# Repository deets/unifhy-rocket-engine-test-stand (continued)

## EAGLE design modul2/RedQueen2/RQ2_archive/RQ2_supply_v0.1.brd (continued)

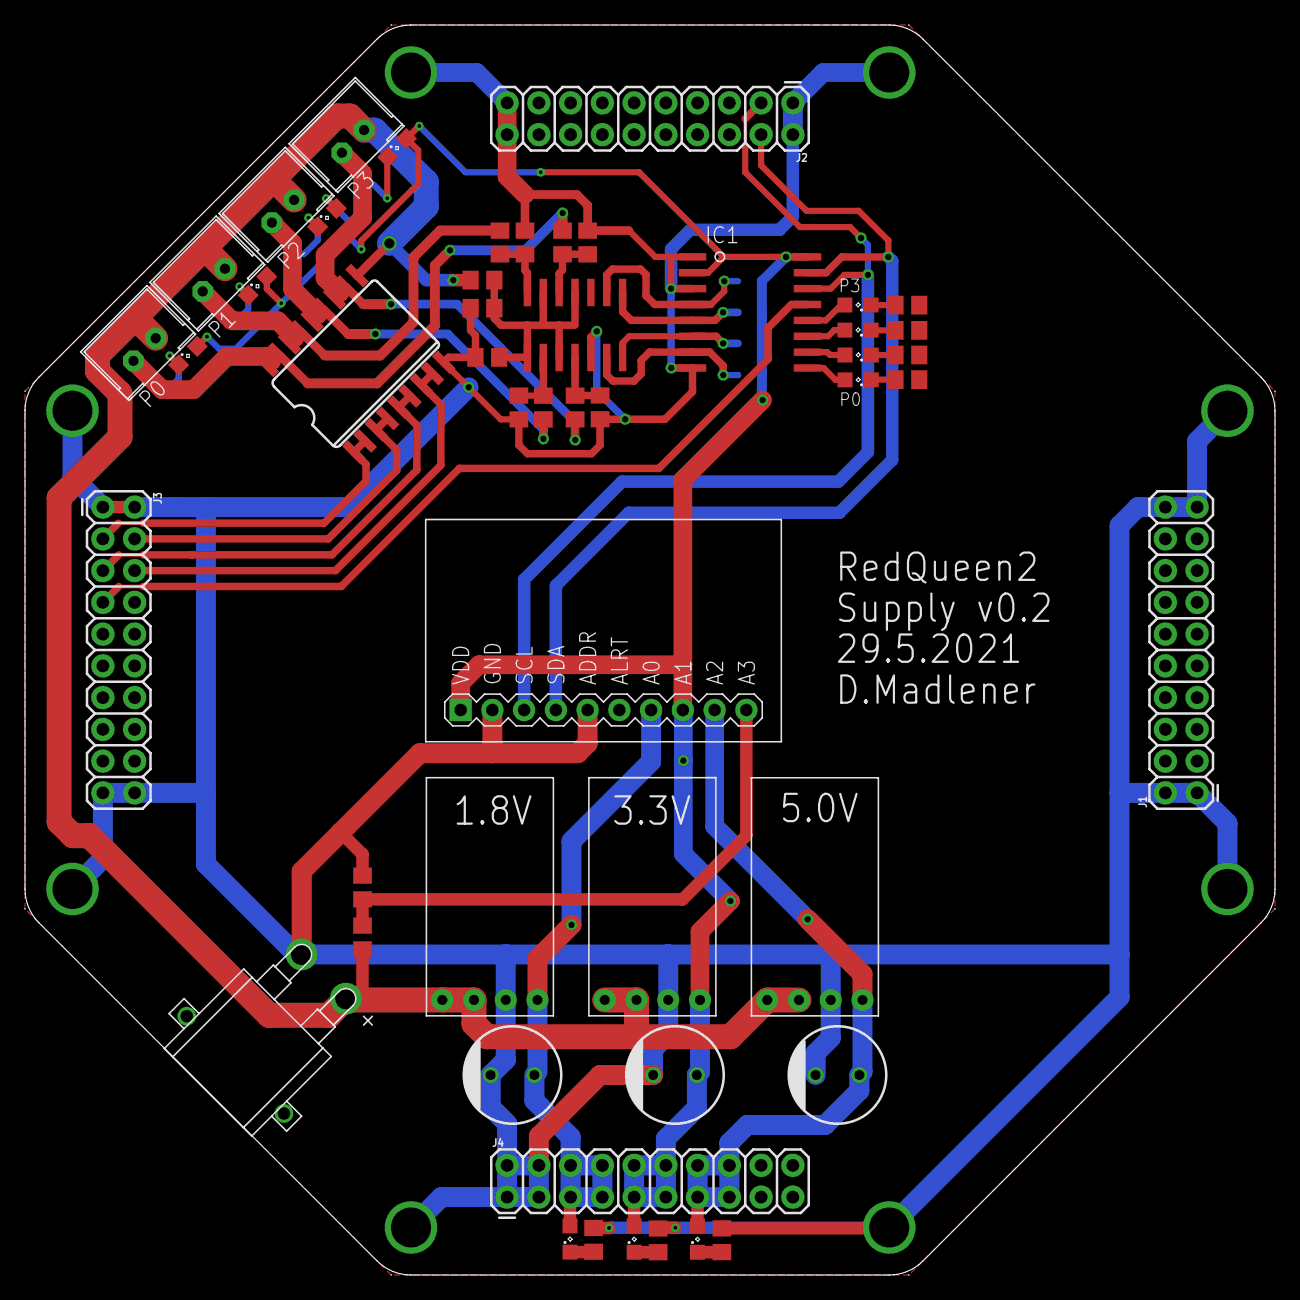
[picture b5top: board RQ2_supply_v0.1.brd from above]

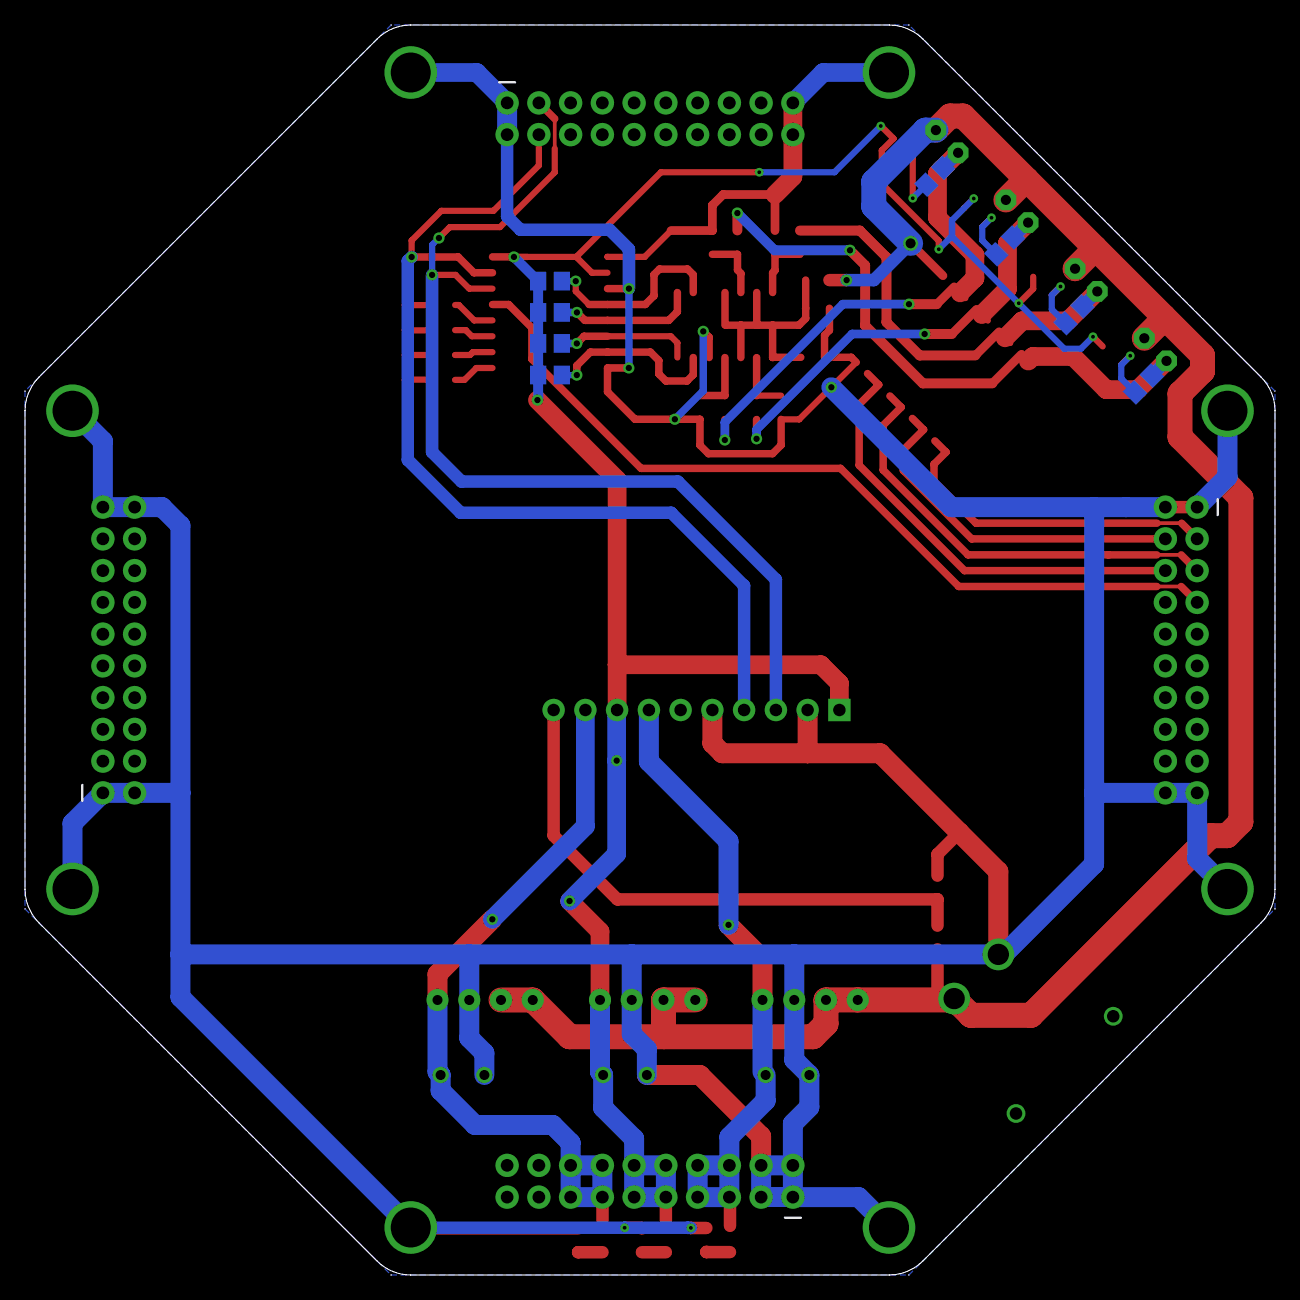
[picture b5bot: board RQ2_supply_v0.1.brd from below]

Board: 2 copper layers, 100.0 x 100.0 mm, 58 parts (8 on the bottom side), 41 nets.

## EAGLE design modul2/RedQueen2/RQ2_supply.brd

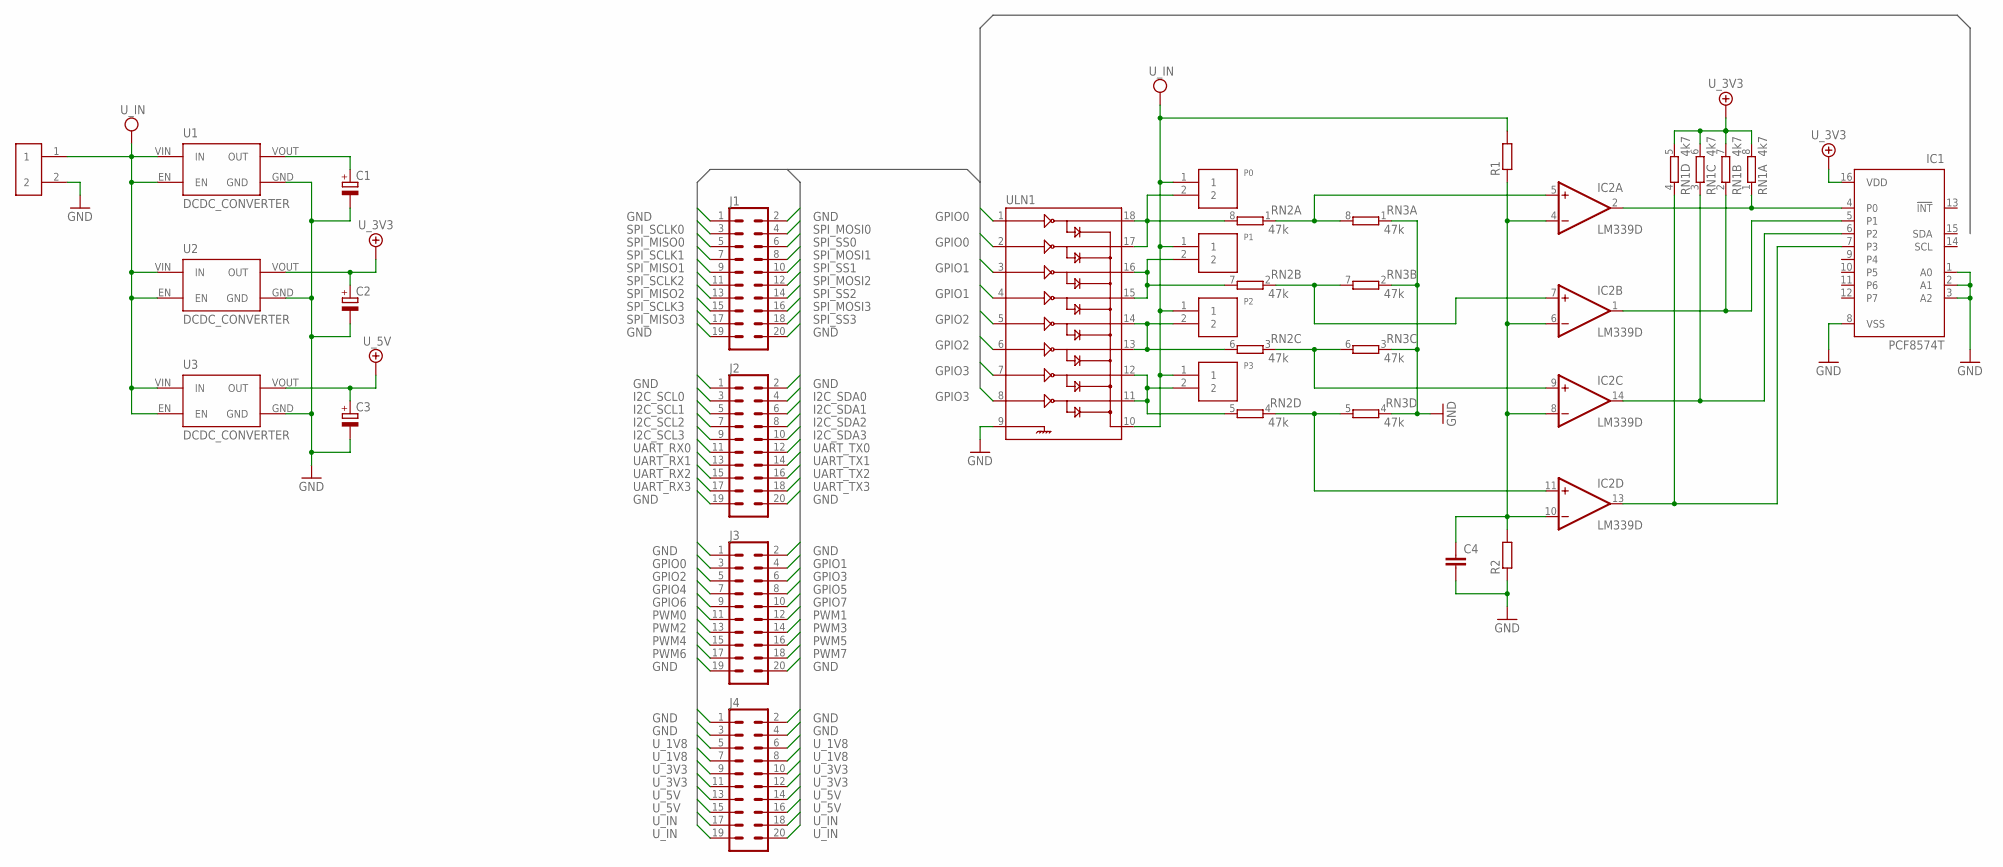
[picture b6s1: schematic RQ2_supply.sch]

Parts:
C1, C2, C3: CPOL-EUC; PANASONIC_C
C4: C-EUC0805; C0805
IC1: PCF8574T; SO16W
IC2: LM339D; SO14
J1, J2, J3, J4: CONN_10X2; 2X10
P0, P1, P2, P3: 2PIN; B2B-PH-K-S
R1, R2: R-EU_R0805; R0805
RN1: 4k7; 0603-ARV
RN2, RN3: 47k; 0603-ARV
U1, U2, U3: DCDC_CONVERTER
U$1: XT_CONN; XT30_PCB
ULN1: ULN2803SOICW; SO18L

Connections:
GND: C1.-, C2.-, C3.-, C4.2, IC1.1 (A0), IC1.2 (A1), IC1.3 (A2), IC1.8 (VSS), IC2.12 (GND), J1.1, J1.2, J1.19, J1.20, J2.1, J2.2, J2.19, J2.20, J3.1, J3.2, J3.19, J3.20, J4.1, J4.2, J4.3, J4.4, R2.1, RN3.1, RN3.2 (1), RN3.3 (1), RN3.4 (1), U1.GND, U2.GND, U3.GND, U$1.2, ULN1.9
GPIO0: J3.3, ULN1.1, ULN1.2
GPIO1: J3.4, ULN1.3, ULN1.4
GPIO2: J3.5, ULN1.5, ULN1.6
GPIO3: J3.6, ULN1.7, ULN1.8
GPIO4: J3.7
GPIO5: J3.8
GPIO6: J3.9
GPIO7: J3.10
I2C_SCL0: J2.3
I2C_SCL1: J2.5
I2C_SCL2: J2.7
I2C_SCL3: J2.9
I2C_SDA0: J2.4
I2C_SDA1: J2.6
I2C_SDA2: J2.8
I2C_SDA3: J2.10
unnamed: IC1.4 (P0), IC2.2 (OUT), RN1.1
unnamed: IC1.5 (P1), IC2.1 (OUT), RN1.2 (1)
unnamed: IC1.6 (P2), IC2.14 (OUT), RN1.3 (1)
unnamed: IC1.7 (P3), IC2.13 (OUT), RN1.4 (1)
unnamed: IC2.5 (+IN), RN2.1, RN3.8 (2)
unnamed: IC2.7 (+IN), RN2.2 (1), RN3.7 (2)
unnamed: IC2.9 (+IN), RN2.3 (1), RN3.6 (2)
unnamed: IC2.11 (+IN), RN2.4 (1), RN3.5 (2)
unnamed: C4.1, IC2.4 (-IN), IC2.6 (-IN), IC2.8 (-IN), IC2.10 (-IN), R1.1, R2.2
PWM0: J3.11
PWM1: J3.12
PWM2: J3.13
PWM3: J3.14
PWM4: J3.15
PWM5: J3.16
PWM6: J3.17
PWM7: J3.18
PYRO0: P0.2, RN2.8 (2), ULN1.17, ULN1.18
PYRO1: P1.2, RN2.7 (2), ULN1.15, ULN1.16
PYRO2: P2.2, RN2.6 (2), ULN1.13, ULN1.14
PYRO3: P3.2, RN2.5 (2), ULN1.11, ULN1.12
SPI_MISO0: J1.5
SPI_MISO1: J1.9
SPI_MISO2: J1.13
SPI_MISO3: J1.17
SPI_MOSI0: J1.4
SPI_MOSI1: J1.8
SPI_MOSI2: J1.12
SPI_MOSI3: J1.16
SPI_SCLK0: J1.3
SPI_SCLK1: J1.7
SPI_SCLK2: J1.11
SPI_SCLK3: J1.15
SPI_SS0: J1.6
SPI_SS1: J1.10
SPI_SS2: J1.14
SPI_SS3: J1.18
UART_RX0: J2.11
UART_RX1: J2.13
UART_RX2: J2.15
UART_RX3: J2.17
UART_TX0: J2.12
UART_TX1: J2.14
UART_TX2: J2.16
UART_TX3: J2.18
U_1V8: C1.+, J4.5, J4.6, J4.7, J4.8, U1.VOUT (OUT)
U_3V3: C2.+, IC1.16 (VDD), J4.9, J4.10, J4.11, J4.12, RN1.5 (2), RN1.6 (2), RN1.7 (2), RN1.8 (2), U2.VOUT (OUT)
U_5V: C3.+, J4.13, J4.14, J4.15, J4.16, U3.VOUT (OUT)
U_IN: J4.17, J4.18, J4.19, J4.20, P0.1, P1.1, P2.1, P3.1, R1.2, U1.EN, U1.VIN (IN), U2.EN, U2.VIN (IN), U3.EN, U3.VIN (IN), U$1.1, ULN1.10
V+: IC2.3 (V+)

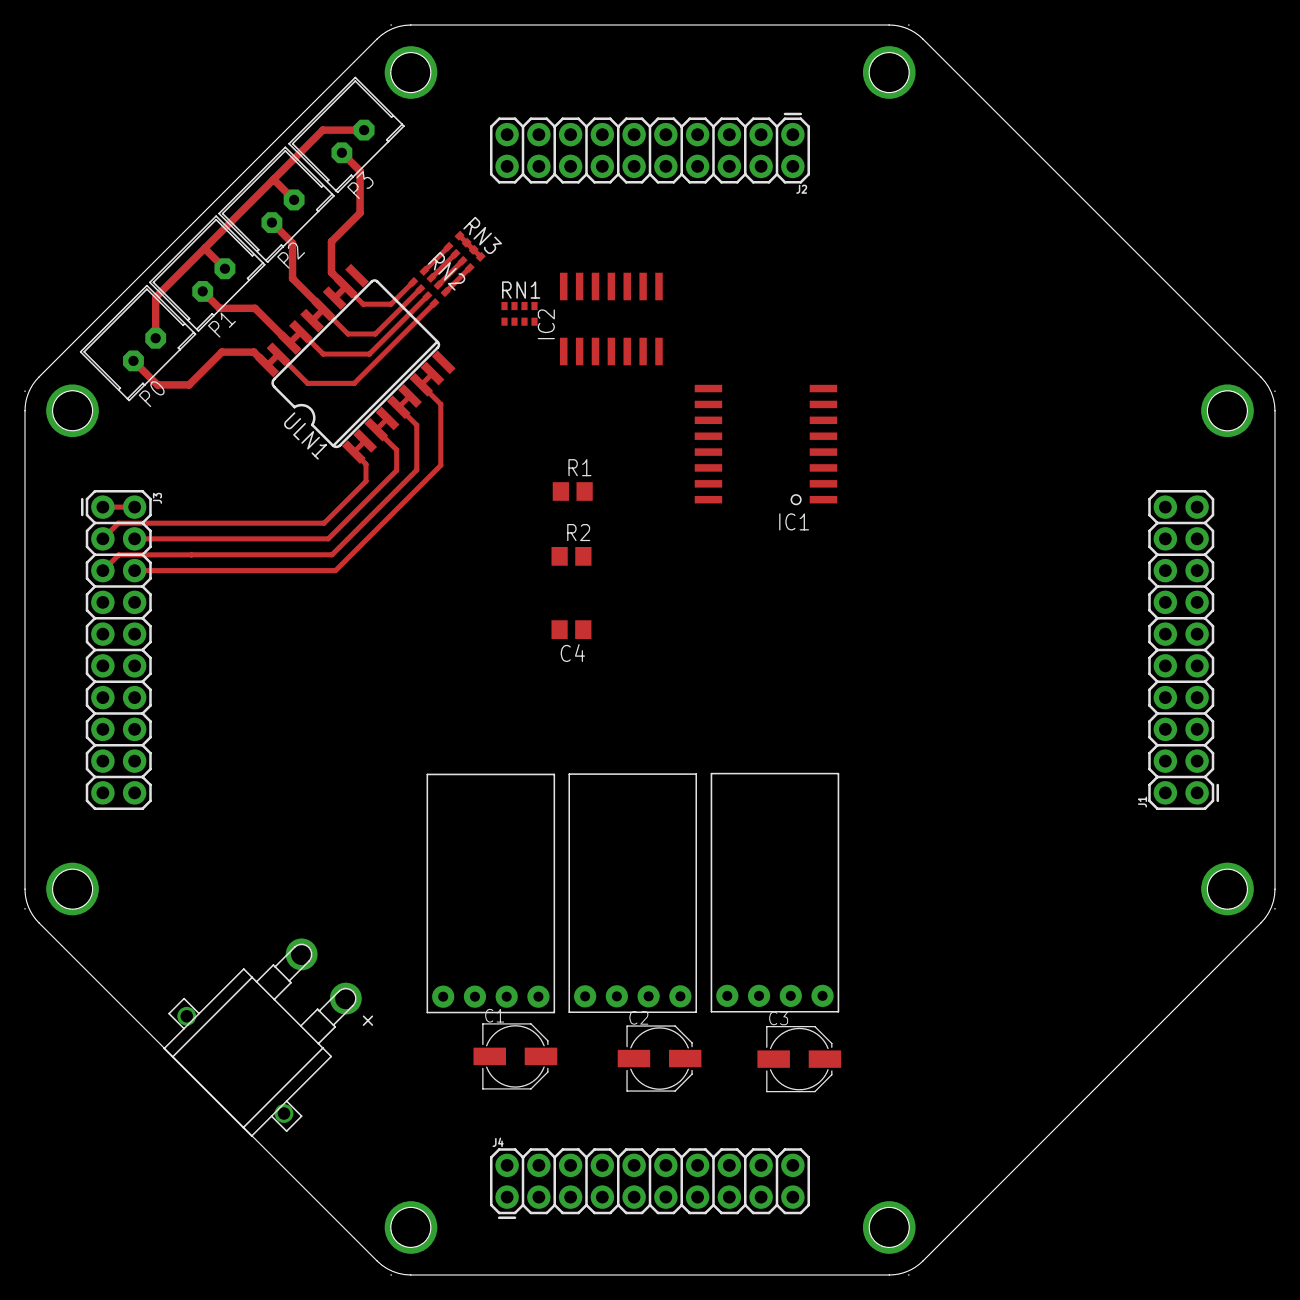
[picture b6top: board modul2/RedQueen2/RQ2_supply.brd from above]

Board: 2 copper layers, 100.0 x 100.0 mm, 24 parts (0 on the bottom side), 22 nets.

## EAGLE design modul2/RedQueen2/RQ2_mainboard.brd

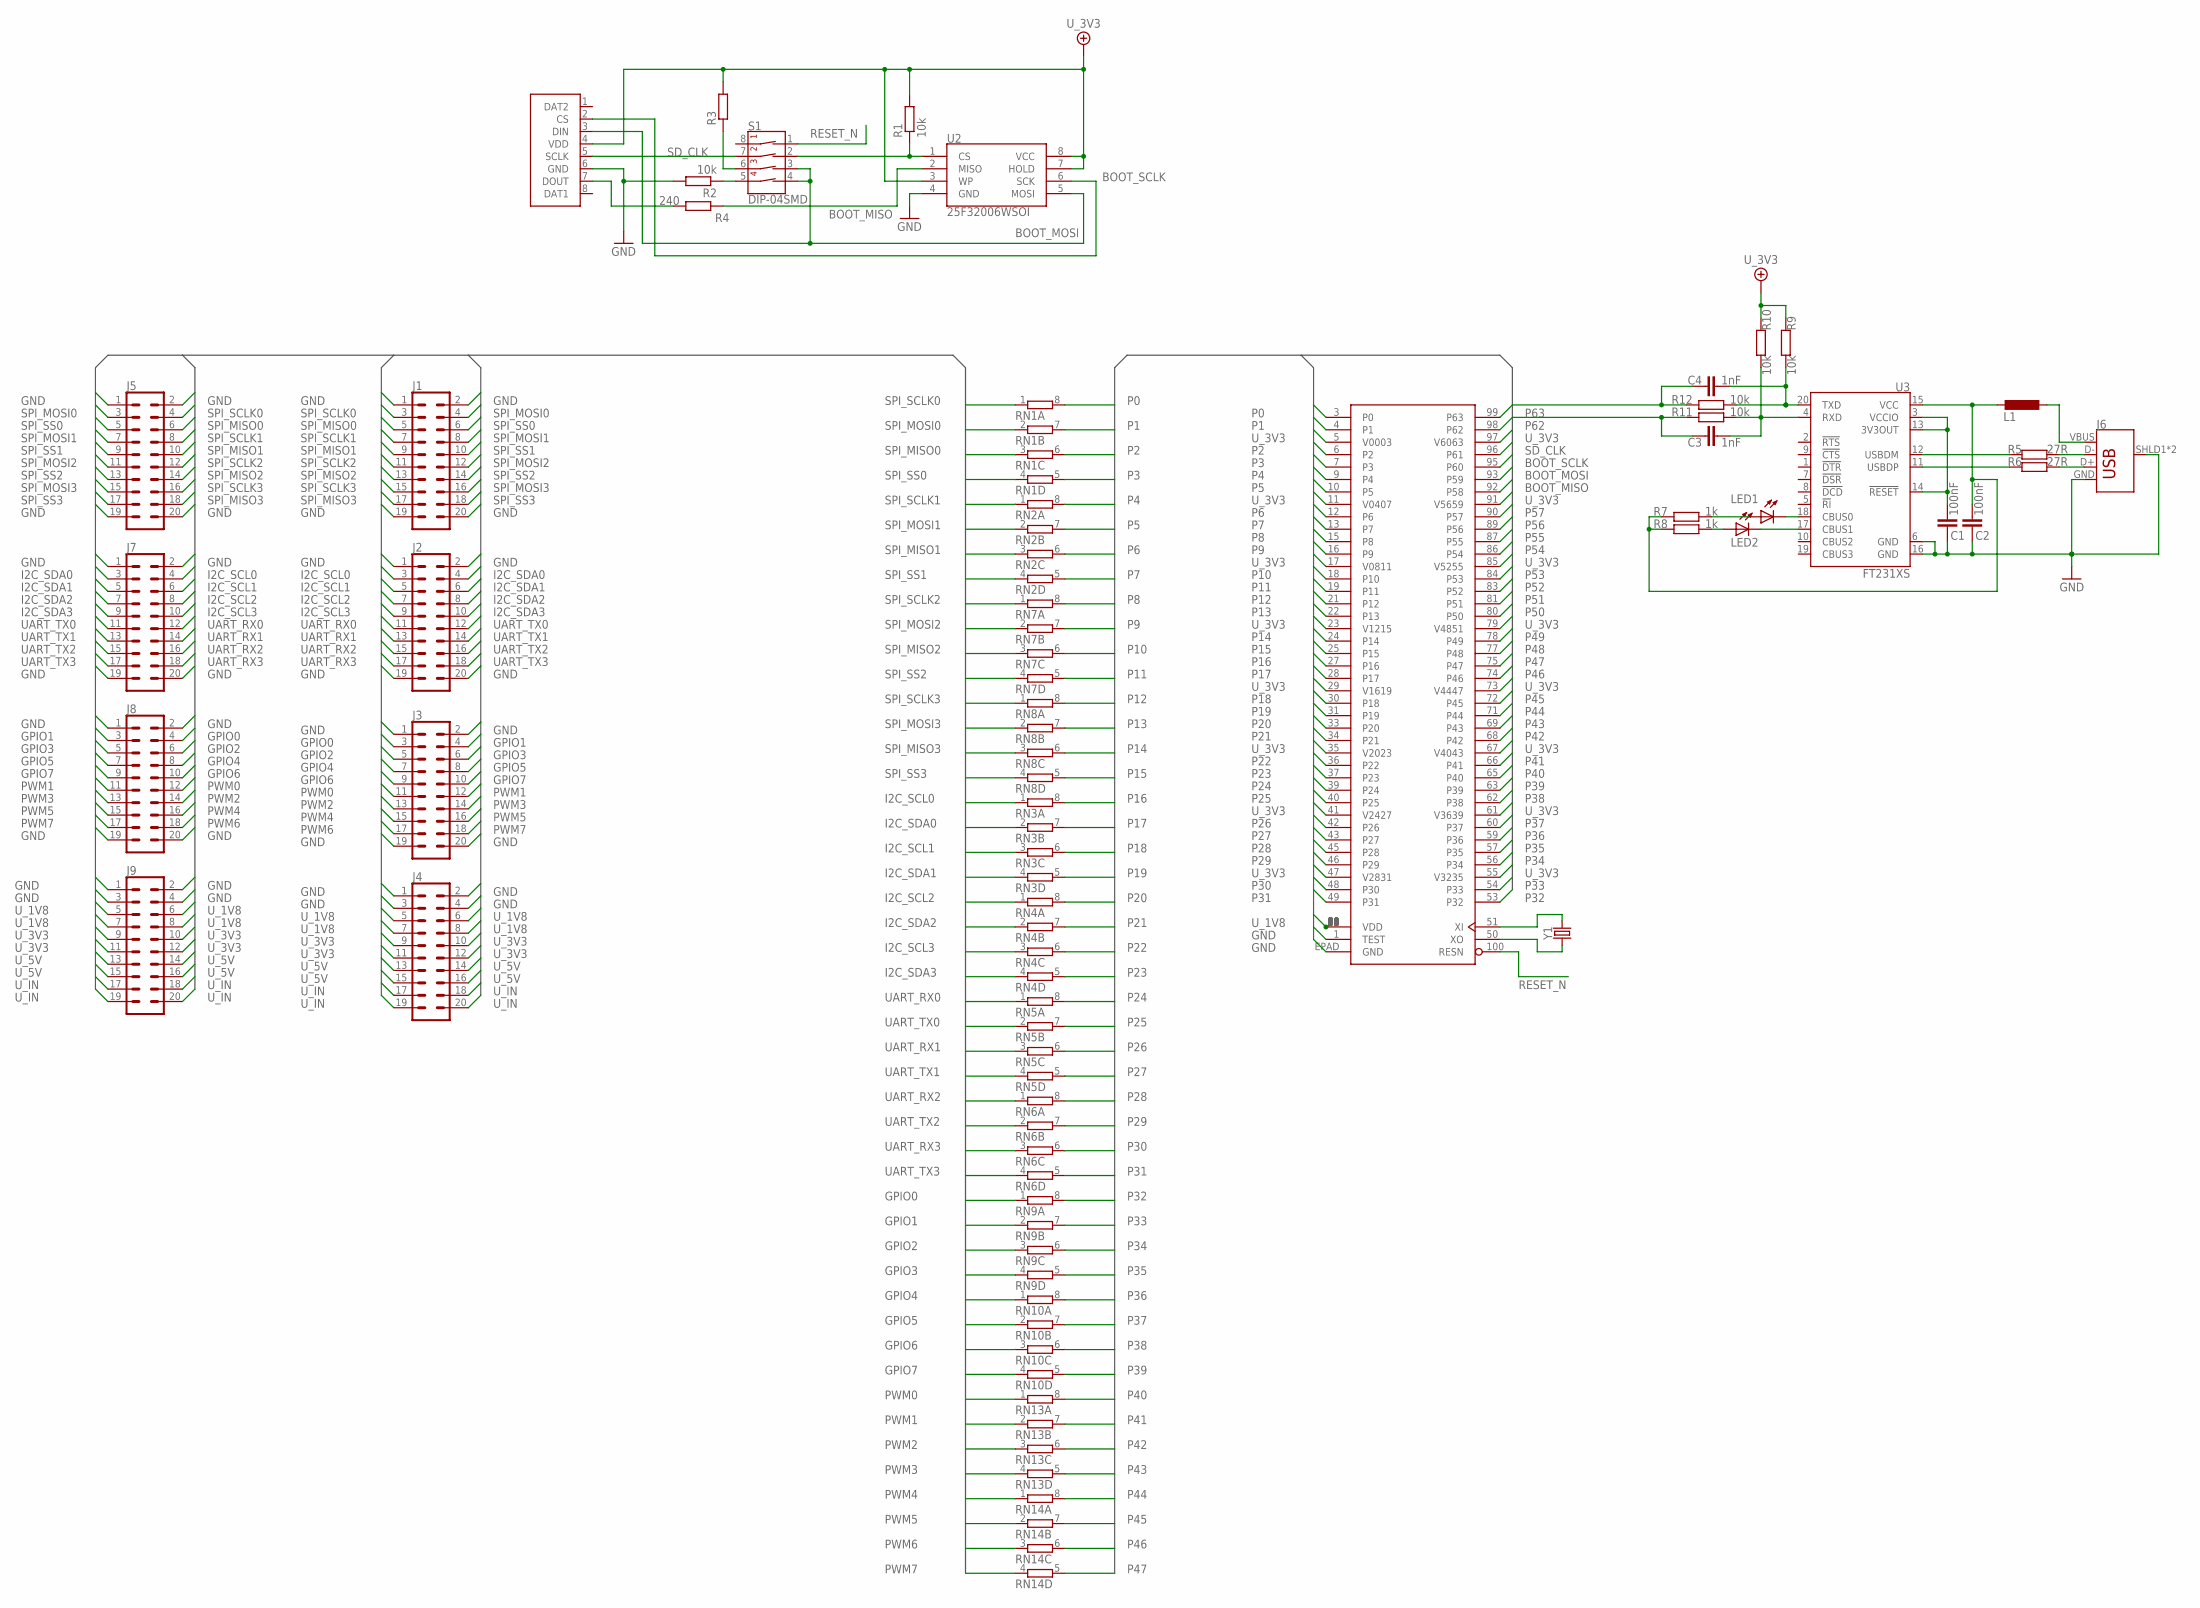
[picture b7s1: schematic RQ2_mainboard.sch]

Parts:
C1, C2: 100nF; C0805
C3, C4: 1nF; C0805
J1, J2, J3, J4, J5, J7, J8, J9: CONN_10X2SMT; 2X10_SMT
J6: USB_B_PTH; USB-B-PTH
L1: L-EUL2012C; L2012C
LED1, LED2: LEDSML0805; SML0805
R1, R2, R9, R10, R11, R12: 10k; R0603
R3: R-EU_R0603; R0603
R4: 240; R0603
R5, R6: 27R; R0603
R7, R8: 1k; R0603
RN1, RN2, RN3, RN4, RN5, RN6, RN7, RN8, RN9, RN10, RN13, RN14: 4R-N0603-ARV; 0603-ARV
S1: DIP-04SMD; DIPSWITCH-04-SMD
U1: P2X8C4M64P; TQFP100
U2: 25F32006WSOI; SO08-EIAJ
U3: FT231XS; SSOP20_L
U$2: MICRO_SD_CONNECTORMOLEX_HINGE; MICRO_SD
Y1: CRYSTALSMD-5X3.2-2PAD; CRYSTAL-SMD-5X3.2-2PAD

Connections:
BOOT_MISO: R4.1, U1.92 (P58), U2.2 (MISO)
BOOT_MOSI: S1.3 (3A), S1.4 (4A), U1.93 (P59), U2.5 (MOSI), U$2.3 (DIN)
BOOT_SCLK: U1.95 (P60), U2.6 (SCK), U$2.2 (CS)
CBUS0: LED1.C, U3.18 (CBUS0)
CBUS1: LED2.C, U3.17 (CBUS1)
D_M: J6.D-, R5.2
D_P: J6.D+, R6.2
FLASH_CS: R1.1, S1.2 (2A), U2.1 (CS)
GND: C1.2, C2.2, J1.1, J1.2, J1.19, J1.20, J2.1, J2.2, J2.19, J2.20, J3.1, J3.2, J3.19, J3.20, J4.1, J4.2, J4.3, J4.4, J5.1, J5.2, J5.19, J5.20, J6.GND, J6.SHLD1 (SHIELD), J6.SHLD2 (SHIELD), J7.1, J7.2, J7.19, J7.20, J8.1, J8.2, J8.19, J8.20, J9.1, J9.2, J9.3, J9.4, R2.2, U1.1 (TEST), U1.EPAD (GND), U2.4 (GND), U3.6 (GND), U3.16 (GND), U$2.6 (GND)
GPIO0: J3.3, J8.4, RN9.1
GPIO1: J3.4, J8.3, RN9.2 (1)
GPIO2: J3.5, J8.6, RN9.3 (1)
GPIO3: J3.6, J8.5, RN9.4 (1)
GPIO4: J3.7, J8.8, RN10.1
GPIO5: J3.8, J8.7, RN10.2 (1)
GPIO6: J3.9, J8.10, RN10.3 (1)
GPIO7: J3.10, J8.9, RN10.4 (1)
I2C_SCL0: J2.3, J7.4, RN3.1
I2C_SCL1: J2.5, J7.6, RN3.3 (1)
I2C_SCL2: J2.7, J7.8, RN4.1
I2C_SCL3: J2.9, J7.10, RN4.3 (1)
I2C_SDA0: J2.4, J7.3, RN3.2 (1)
I2C_SDA1: J2.6, J7.5, RN3.4 (1)
I2C_SDA2: J2.8, J7.7, RN4.2 (1)
I2C_SDA3: J2.10, J7.9, RN4.4 (1)
LED1: LED1.A, R7.2
LED2: LED2.A, R8.2
unnamed: R2.1, S1.5 (4B)
unnamed: R3.1, S1.6 (3B)
unnamed: R4.2, U$2.7 (DOUT)
P0: RN1.8 (2), U1.3 (P0)
P1: RN1.7 (2), U1.4 (P1)
P2: RN1.6 (2), U1.6 (P2)
P3: RN1.5 (2), U1.7 (P3)
P4: RN2.8 (2), U1.9 (P4)
P5: RN2.7 (2), U1.10 (P5)
P6: RN2.6 (2), U1.12 (P6)
P7: RN2.5 (2), U1.13 (P7)
P8: RN7.8 (2), U1.15 (P8)
P9: RN7.7 (2), U1.16 (P9)
P10: RN7.6 (2), U1.18 (P10)
P11: RN7.5 (2), U1.19 (P11)
P12: RN8.8 (2), U1.21 (P12)
P13: RN8.7 (2), U1.22 (P13)
P14: RN8.6 (2), U1.24 (P14)
P15: RN8.5 (2), U1.25 (P15)
P16: RN3.8 (2), U1.27 (P16)
P17: RN3.7 (2), U1.28 (P17)
P18: RN3.6 (2), U1.30 (P18)
P19: RN3.5 (2), U1.31 (P19)
P20: RN4.8 (2), U1.33 (P20)
P21: RN4.7 (2), U1.34 (P21)
P22: RN4.6 (2), U1.36 (P22)
P23: RN4.5 (2), U1.37 (P23)
P24: RN5.8 (2), U1.39 (P24)
P25: RN5.7 (2), U1.40 (P25)
P26: RN5.6 (2), U1.42 (P26)
P27: RN5.5 (2), U1.43 (P27)
P28: RN6.8 (2), U1.45 (P28)
P29: RN6.7 (2), U1.46 (P29)
P30: RN6.6 (2), U1.48 (P30)
P31: RN6.5 (2), U1.49 (P31)
P32: RN9.8 (2), U1.53 (P32)
P33: RN9.7 (2), U1.54 (P33)
P34: RN9.6 (2), U1.56 (P34)
P35: RN9.5 (2), U1.57 (P35)
P36: RN10.8 (2), U1.59 (P36)
P37: RN10.7 (2), U1.60 (P37)
P38: RN10.6 (2), U1.62 (P38)
P39: RN10.5 (2), U1.63 (P39)
P40: RN13.8 (2), U1.65 (P40)
P41: RN13.7 (2), U1.66 (P41)
P42: RN13.6 (2), U1.68 (P42)
P43: RN13.5 (2), U1.69 (P43)
P44: RN14.8 (2), U1.71 (P44)
P45: RN14.7 (2), U1.72 (P45)
P46: RN14.6 (2), U1.74 (P46)
P47: RN14.5 (2), U1.75 (P47)
P48: U1.77 (P48)
P49: U1.78 (P49)
P50: U1.80 (P50)
P51: U1.81 (P51)
P52: U1.83 (P52)
P53: U1.84 (P53)
P54: U1.86 (P54)
P55: U1.87 (P55)
P56: U1.89 (P56)
P57: U1.90 (P57)
P62: C3.1, R11.1, U1.98 (P62)
P63: C4.1, R12.1, U1.99 (P63)
PWM0: J3.11, J8.12, RN13.1
PWM1: J3.12, J8.11, RN13.2 (1)
PWM2: J3.13, J8.14, RN13.3 (1)
PWM3: J3.14, J8.13, RN13.4 (1)
PWM4: J3.15, J8.16, RN14.1
PWM5: J3.16, J8.15, RN14.2 (1)
PWM6: J3.17, J8.18, RN14.3 (1)
PWM7: J3.18, J8.17, RN14.4 (1)
RESET_N: S1.1 (1A), U1.100 (RESN)
SD_CLK: S1.7 (2B), U1.96 (P61), U$2.5 (SCLK)
SPI_MISO0: J1.5, J5.6, RN1.3 (1)
SPI_MISO1: J1.9, J5.10, RN2.3 (1)
SPI_MISO2: J1.13, J5.14, RN7.3 (1)
SPI_MISO3: J1.17, J5.18, RN8.3 (1)
SPI_MOSI0: J1.4, J5.3, RN1.2 (1)
SPI_MOSI1: J1.8, J5.7, RN2.2 (1)
SPI_MOSI2: J1.12, J5.11, RN7.2 (1)
SPI_MOSI3: J1.16, J5.15, RN8.2 (1)
SPI_SCLK0: J1.3, J5.4, RN1.1
SPI_SCLK1: J1.7, J5.8, RN2.1
SPI_SCLK2: J1.11, J5.12, RN7.1
SPI_SCLK3: J1.15, J5.16, RN8.1
SPI_SS0: J1.6, J5.5, RN1.4 (1)
SPI_SS1: J1.10, J5.9, RN2.4 (1)
SPI_SS2: J1.14, J5.13, RN7.4 (1)
SPI_SS3: J1.18, J5.17, RN8.4 (1)
UART_RX0: J2.11, J7.12, RN5.1
UART_RX1: J2.13, J7.14, RN5.3 (1)
UART_RX2: J2.15, J7.16, RN6.1
UART_RX3: J2.17, J7.18, RN6.3 (1)
UART_TX0: J2.12, J7.11, RN5.2 (1)
UART_TX1: J2.14, J7.13, RN5.4 (1)
UART_TX2: J2.16, J7.15, RN6.2 (1)
UART_TX3: J2.18, J7.17, RN6.4 (1)
USBDM: R5.1, U3.12 (USBDM)
USBDP: R6.1, U3.11 (USBDP)
USB_3V3: C1.1, U3.3 (VCCIO), U3.13 (3V3OUT), U3.14 (!RESET)
USB_5V: C2.1, L1.2, R7.1, R8.1, U3.15 (VCC)
USB_RX: C3.2, R10.2, R11.2, U3.4 (RXD)
USB_TX: C4.2, R9.2, R12.2, U3.20 (TXD)
U_1V8: J4.5, J4.6, J4.7, J4.8, J9.5, J9.6, J9.7, J9.8, U1.2 (VDD), U1.8 (VDD), U1.14 (VDD), U1.20 (VDD), U1.26 (VDD), U1.32 (VDD), U1.38 (VDD), U1.44 (VDD), U1.52 (VDD), U1.58 (VDD), U1.64 (VDD), U1.70 (VDD), U1.76 (VDD), U1.82 (VDD), U1.88 (VDD), U1.94 (VDD)
U_3V3: J4.9, J4.10, J4.11, J4.12, J9.9, J9.10, J9.11, J9.12, R1.2, R3.2, R9.1, R10.1, U1.5 (V0003), U1.11 (V0407), U1.17 (V0811), U1.23 (V1215), U1.29 (V1619), U1.35 (V2023), U1.41 (V2427), U1.47 (V2831), U1.55 (V3235), U1.61 (V3639), U1.67 (V4043), U1.73 (V4447), U1.79 (V4851), U1.85 (V5255), U1.91 (V5659), U1.97 (V6063), U2.3 (WP), U2.7 (HOLD), U2.8 (VCC), U$2.4 (VDD)
U_5V: J4.13, J4.14, J4.15, J4.16, J9.13, J9.14, J9.15, J9.16
U_IN: J4.17, J4.18, J4.19, J4.20, J9.17, J9.18, J9.19, J9.20
VBUS: J6.VBUS, L1.1
XIN: U1.51 (XI), Y1.P$2 (2)
XOUT: U1.50 (XO), Y1.P$1 (1)

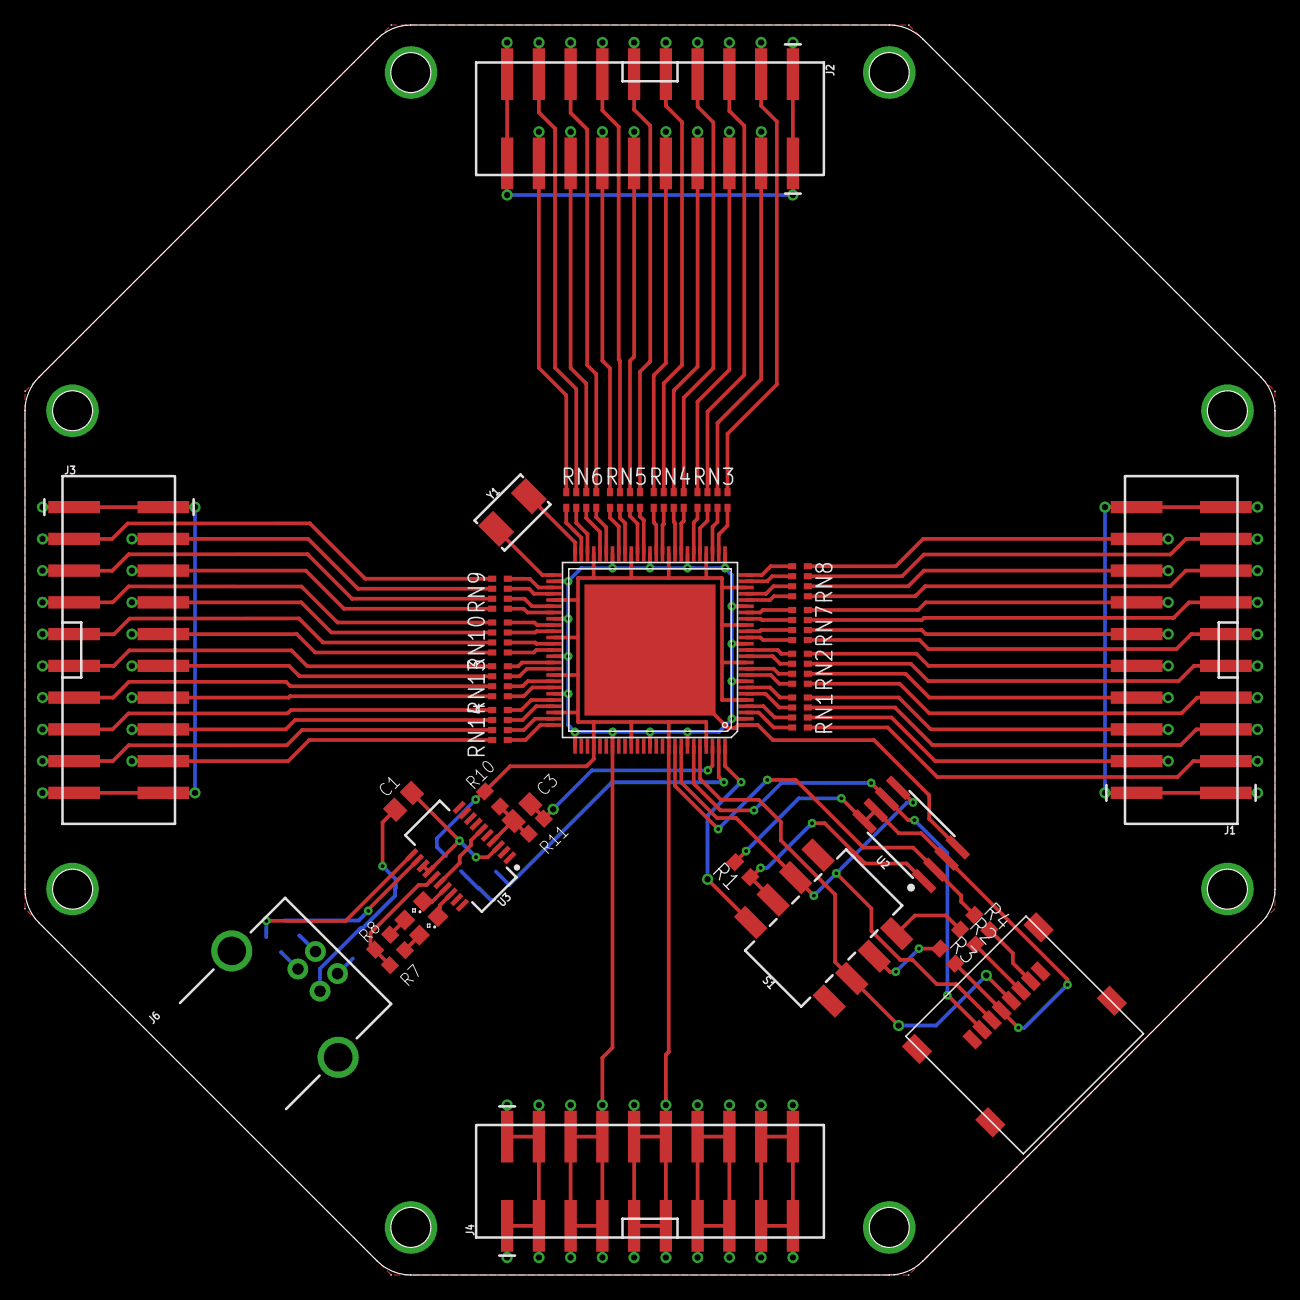
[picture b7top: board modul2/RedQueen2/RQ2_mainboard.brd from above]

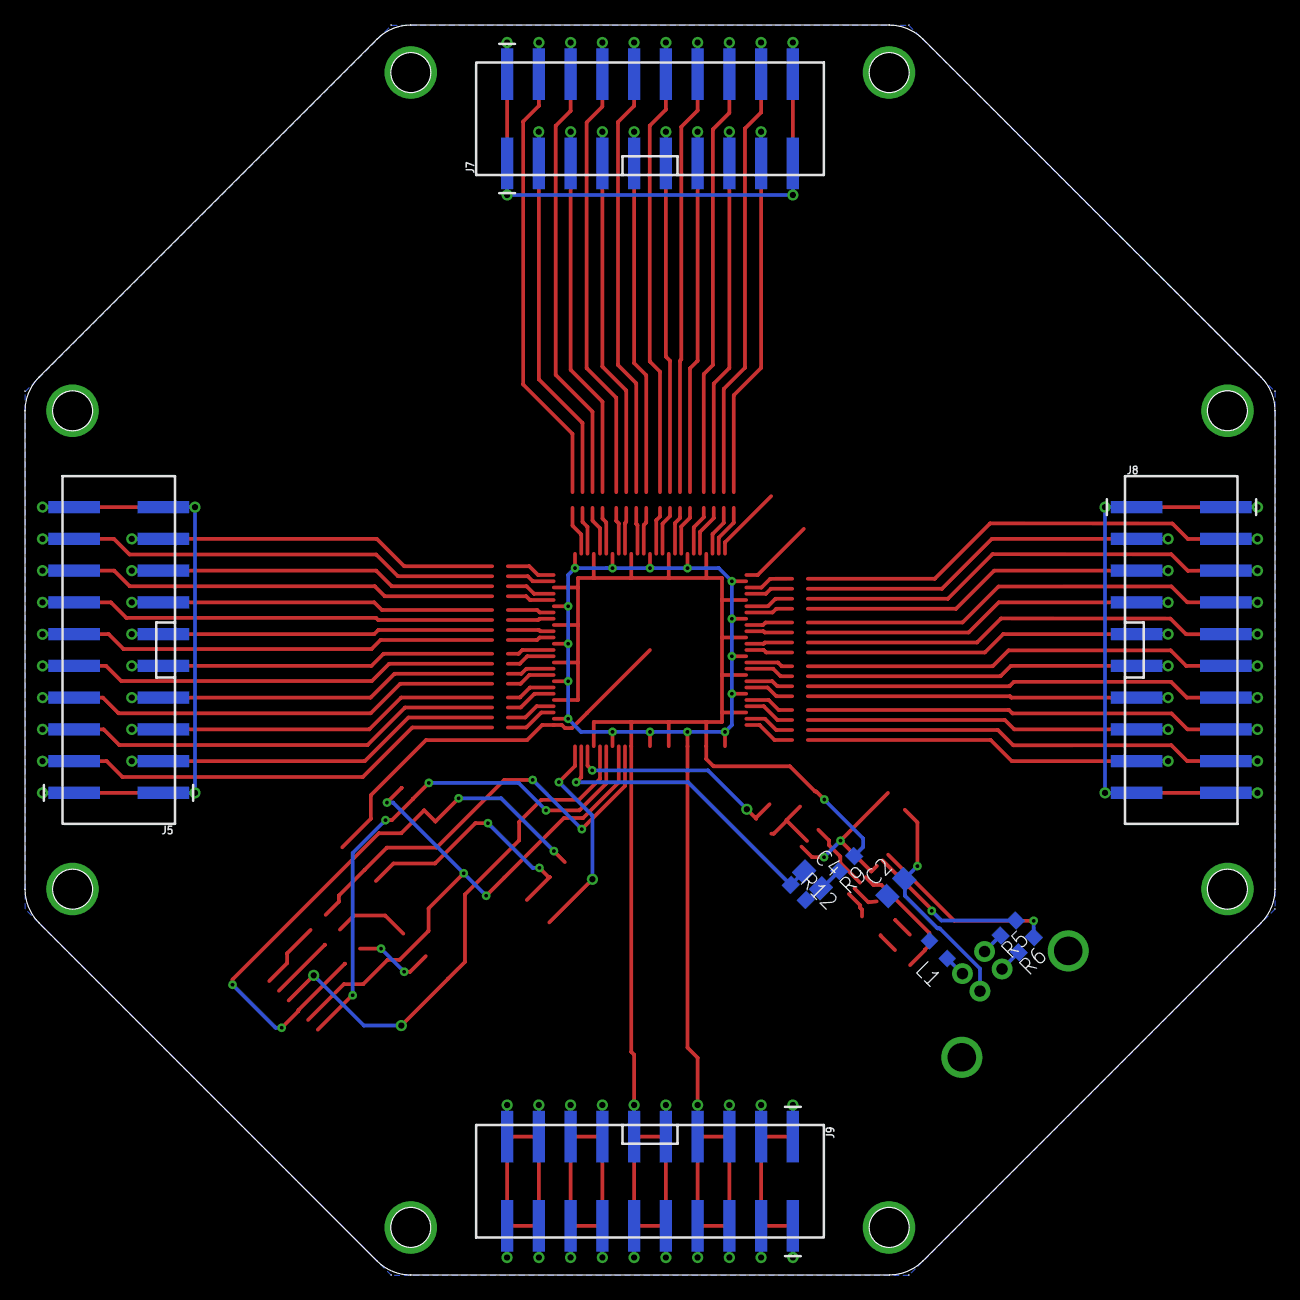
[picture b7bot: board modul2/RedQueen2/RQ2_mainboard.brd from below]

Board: 2 copper layers, 100.0 x 100.0 mm, 46 parts (11 on the bottom side), 127 nets.

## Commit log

2020-02-29 Introduce ringbuffer class
2020-02-29 Add arduino layer as component
2020-02-29 Initial commit - 500us loop with 9 long words SPI communication
2020-02-29 Dynamic period to wait when sampling
2020-02-29 Introduce data-logger and signal sampler task
2020-02-29 Convert data sampler into class
2020-02-29 Renamed task
2020-02-29 Add WIFI to the mix
    Also use polling transactions & retry to mount the SD-Card
    Wifi deteriorates the SPI task timing. Will have to investigate.
2020-02-29 Set up SD-card reading
2020-02-29 Switch to different SPI channel and hardware CS
2020-02-29 Add a tiny description
2020-02-29 Enhance datalogger to write strings using ADL
2020-06-01 Implement DataLogger as Task
2020-06-01 Move ESP32 test balloon into own subdirectory
2020-06-05 Erste Schritte Dokumentation
2020-06-10 First commit of Modul3 Software
2020-06-10 Etwas GIT Dokumentation
2020-06-10 Datenblatt des ADC
2020-06-21 Add some images
2020-08-05 Add WIFI to the mix
2020-08-05 Moved to modul2 subfolder
2020-08-05 Upgrade to IDF 3.3.2
2020-09-29 RQ2 commit #1
    New Eagle boards and schematics, RedQueen 2 mainboard and supply
2021-03-05 Add some documentation about the ADS1256 breakout board
2021-03-05 P2 hello world with extra serial
    The extra serial is because I currently can't flash but only load to
    memory.
2021-03-07 Began implementing ADS1256 in spin2
    So far only the physical setup is mimicked and according to the
    logic analyser, the communication looks good.
2021-03-08 Read single channel conversion result
2021-03-08 Cleanup and fix bug in WREG
    It appears one needs to wait for DRDY LOW before a register can be written.
2021-03-13 Implemented buffered interface on top of existing ADS1256 code
2021-03-14 Implement the continuous acquisition mode
2021-03-14 Remove warnings after introducing -Wall
2021-03-21 Working ringbuffer and verified >4K data acquisition speed
2021-03-21 Start working on the RQ serial protocol
2021-03-28 Start work on serial protocol
2021-03-28 Ignore build-directory
2021-03-28 Improve documentation a bit
2021-03-28 Implement first command: P for PING, returns a P for PONG
2021-05-30 First introduction of SD-Card/FAT32 code
2021-05-30 Implement the R command
    This allows to set the samplerate
2021-05-30 Beginnings of the continuous acquisition
2021-05-30 Implement thinning
2021-05-30 Continuous data acquisition should work now
2021-05-30 Add P2 Eval Board schematic
2021-06-04 Move to colons vs dollarsigns as separators, as suggested by David
2021-06-04 Introduce the SD Writer and figure out the index of the next file to create
2021-06-04 Introduce cmd architecture and create new file
2021-06-05 Refactor: introduce util object and use it throughout
2021-06-05 Cleanup: docstring
2021-06-05 Signify the synchronous nature of the begin call
2021-06-05 Basic SD card writing works
    Currently the 30K SPS mode does not seem to properly work, but
    we *do* write stuff!
2021-06-09 Pull in dependencies so others can build
2021-06-11 Writing of data works at full speed
2021-06-11 Smaller ringbuffer, seems still to be enough
2021-06-13 Remove audio DAC code
2021-06-18 Pull startswith/endswith into util and add timediff
2021-06-18 Increase clkfreq to 300_000_000
2021-06-18 Fix linesize and report SD card status via LED
2021-06-18 Remove dead/unused code
2021-06-18 Never allow timestamp 0 so we can use it as sentinel value
2021-06-18 DROPME: Mark block-writing with pin
2021-06-19 Flush after one sector
2021-06-19 Communicate run statistics and write it as last line
2021-06-19 Introduce a running-flag to allow for non-sd-card operation
2021-06-19 Introduce reps and duration and a statistics call as finalization
2021-06-19 Gather statistics during the run and offer them via S-command
2021-06-19 Seed the avg_timediff with a value based on the actual data rate
2021-06-19 Re-organize code so that obtaining the expected timediff works
2021-06-20 Start Connector Implementation
2021-06-20 Implement listing files
2021-06-20 Align debugging statement output with last file line order
2021-06-20 Add size to file listing
2021-06-20 Refactor: improve rq_finalize, no argument anymore
2021-06-20 Implement streaming files via serial line
2021-06-20 Start to implement proper interface for starting/stopping of data acquistion
2021-06-26 Make sdwriter take callbacks to the ringbuffer
    This allows for easy swapping of the ringbuffer implementation
2021-06-26 Move up to 1_000_000 BPS for serial communication
2021-06-26 Trick flexspin code generation to return actual file size
    This removes the need for the debug-mode
2021-06-27 Replace ringbuffer with hyper_ringbuffer
2021-06-27 Improve sdwriter
    This includes a rather ugly workaround for the WAITATN that
    fails me in the end()-method
2021-06-27 Some changes to the test script
2021-06-27 Some data display script
2021-06-27 Add HyperRAM driver
2021-06-27 Comment out a lot of debug statements
2021-06-27 Apply wuerfel_21 fix that isn't confusing code generation
2021-06-27 Add a HyperRAM ringbuffer implementation
    This includes a test that seems to indicate things are working
2021-07-03 changed variable name to enable compilation with Propeller Tool
2021-07-03 just some minor changes to enable compiling with Propeller Tool
2021-07-04 Fix bug with not waiting for serial streaming to finish
2021-07-04 It seems this is working to write 10 seconds of data
2021-07-04 Removed superfluous terminal commands
2021-07-04 Test pin reading
2021-07-04 Introduce SD card and write to it based on the second button
2021-07-04 Clarify names
2021-07-04 Adding a serial output to stream the data away
    This shows that the data is buffered properly
2021-07-04 Trigger data acquisition by button
2021-07-04 Stream the data file line format over serial
2021-07-04 Remove polluting debug statement
2021-07-04 Don't write the data to the SD-card
    This leads to a situation where the data is broken in the beginning
    (presumably during FAT setup) but then starts to become well-formed
    again.
2021-07-04 Moved to new getct()
2021-07-04 Comment out debug commands
2021-07-04 Enlargen line buffer
2021-07-04 Compute biggest diff also when showing the data
2021-07-04 Added reset call to ringbuffer and use it
2021-07-04 Add a tiny stats functionality to the buffered ADS
    This determines the biggest difference between two consecutive
    values. It serves as sanity check in the data corruption
    investigation.
2021-07-07 Fix bug that left a lingering value in the ringbuffer.
    Now it will always be cleared out at the beginning of a continuous acquisition.
2021-07-08 Upper case filenames
2021-07-08 Move HyperRAM to new base and add a little selftest
2021-07-08 Adapt code to the new base for the accessory boards
2021-07-08 Add a simple "linear" clock that just uses an index instead of timestamps
2021-10-12 Update copyright info
    JonnyMac explicitly expressed his wish to not be affiliated
    with derivatives of his code.
2021-10-12 Introduce configuration object
    This depends on a preprocessor variable to select the target board
2021-10-14 Begin working on switched frontend
2021-10-14 Introduce capturing switch
2021-10-18 Fix some timing constants
2021-10-18 Clearer status names
2021-10-18 Use the MUX-method even for single channel data acquisition
    It might be preferable to use RDATAC instead, but for now
    this seems to work well enough and we are expecting multi channel
    reading anyway
2021-10-18 Implement switched frontend
2021-10-18 Intorduce and use convenience method to set the samplerate
    Also improve flashtime by making the ADC buffer smaller - it
    was inflated during debugging.
2021-10-18 Fall out of capturing when the capacity is exhausted
2021-10-24 Refactor status and account for the two cogs driving it.
2022-01-02 Begin cleanup of SD card driver
2022-01-02 wip: debug pin to signify the start of the driver
2022-01-02 Spin2 frontend for sd card cleanup
2022-01-02 Unify handling of R3/R7 responses (R1 + 4 bytes)
2022-01-03 multi blocks beginning
2022-01-30 Move toward ESP SDK 4.2 in an attempt to get faster SD card writes
2022-02-06 Write block-wise to the SD-card
2022-02-12 Enhance sd card writing code based on my ESP32 investigation
2022-02-12 Lower SD-card frequency for better analysis with my logic analyser
2022-02-12 Write based on button-press for simple recording workflow
2022-02-12 Renamed and use parameter for bitwait
2022-02-20 Add KiCad project from mainboard
2022-02-20 Add supply board
2022-03-29 Update (C) notice
2022-03-29 Comment about maximum SPI speed on P2 Eval Rev C
2022-03-29 Prefix SD Card commands for clarity and name collision avoidance
2022-03-29 Remove DEBUG_PIN
2022-03-29 Consistent method names
2022-03-29 Remove superfluous variable
2022-03-29 Add UNIFHY configuration
2022-03-29 Clarified mount code
2022-03-29 Modify frontend to allow for a range of commands
2022-03-29 Pass speed as argument
2022-03-29 Hook my SD SPI code into FAT32
2022-03-30 Fix mountPartition to do what it promises to do and use it
2022-03-30 Introduce l command to list the SD card contents
2022-03-31 Fix FAT32 to conform to the openFile protocol as stated
    Before it would return the filename *or* error string, making
    that hard to decide.
2022-03-31 Implemented dumping file contents
2022-04-07 Minor cleanup and add some clarifying comments.
2022-04-08 Extract strupper and uppercase into util
2022-04-08 Implement write tests with single/multiple block writes
2022-04-08 Start on commandline control of SD card frontend
2022-04-08 Add info command to show some FAT properties.
2022-04-08 Implement filling the large buffer and extend command parsing
2022-04-08 Verify written blocks contain the expected data
2022-04-09 Allow the actual buffer size to be set
    This allows to better compare the single vs multiple block writes.
2022-04-09 Extracted command infrastructure
2022-04-09 Move FAT frontend to command
2022-04-09 Extracted dump_block into util
2022-04-09 Implement writing data into file
2022-06-22 Bump numpy from 1.20.3 to 1.22.0 in /modul2/P2/py
    Bumps [numpy](https://github.com/numpy/numpy) from 1.20.3 to 1.22.0.
    - [Release notes](https://github.com/numpy/numpy/releases)
    - [Changelog](https://github.com/numpy/numpy/blob/main/doc/HOWTO_RELEASE.rst)
    - [Commits](https://github.com/numpy/numpy/compare/v1.20.3...v1.22.0)
    ---
    updated-dependencies:
2023-04-19 RQ2 archived versions
2023-04-19 RQ2 v1.0 files
2023-08-27 Place current version of RQ into repo
2023-08-27 Little FAT32 utility script to format an SD card
2023-08-27 Some work in progress
2023-08-27 Get switched frontend working again
2023-08-27 Fix Qt module
2023-08-27 Use preprocessor to enable/disable HyperRAM
2023-08-27 Fix UNIHFY config and preprocessor defs
